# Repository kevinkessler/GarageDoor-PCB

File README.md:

PCB Eagle Files for Garage Door Spark Core project

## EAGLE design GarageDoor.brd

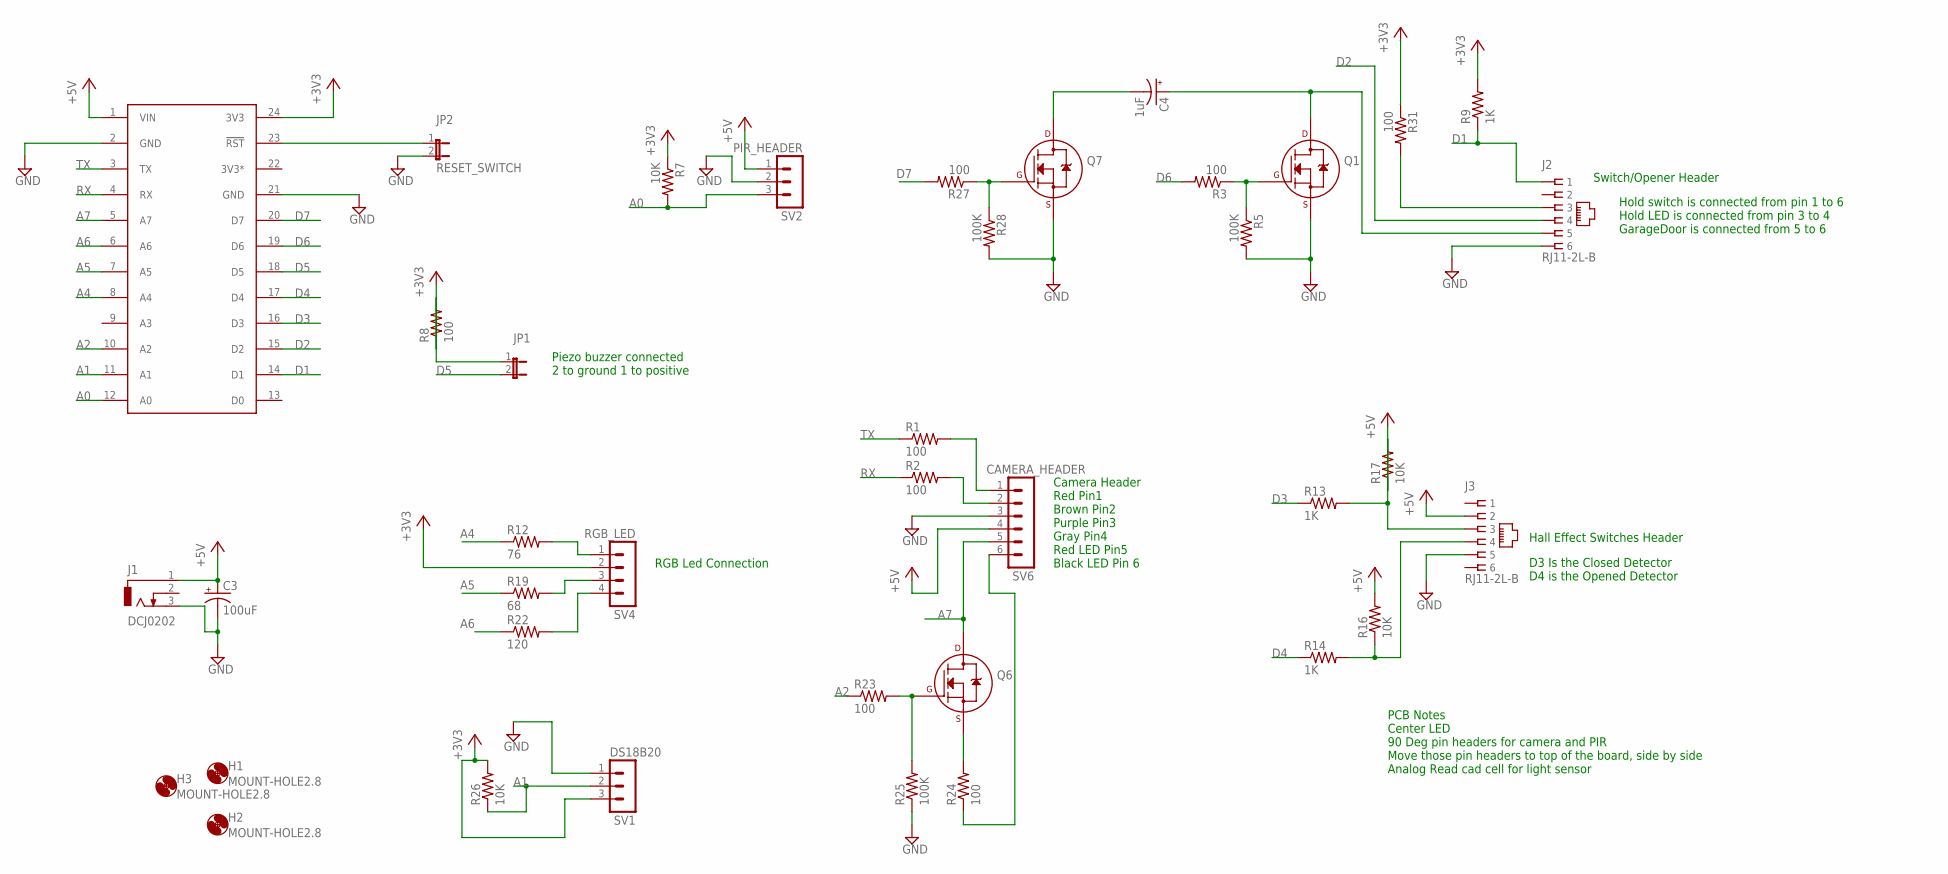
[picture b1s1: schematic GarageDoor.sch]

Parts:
C3: 100uF; E2,5-6E
C4: 1uF; E2,5-6E
H1, H2, H3: MOUNT-HOLE2.8; 2,8
J1: DCJ0202
J2, J3: RJ11-2L-B; RJ11-NO_SHIELD
JP1: JP1E; JP1
JP2: RESET_SWITCH; JP1
Q1, Q6, Q7: 2N7000_SOT23; SOT-23
R1, R2, R3, R8, R23, R24, R27, R31: 100; R0805
R5, R25, R28: 100K; R0805
R7, R16, R17, R26: 10K; R0805
R9, R13, R14: 1K; R0805
R12: 76; R0805
R19: 68; R0805
R22: 120; R0805
SC1: SPARK_CORECORE; SPARK_CORE
SV1: DS18B20; MA03-1
SV2: PIR_HEADER; MA03-1
SV4: RGB_LED; MA04-1
SV6: CAMERA_HEADER; MA06-1

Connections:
3V3*: SC1.22 (3V3*)
+3V3: R7.1, R8.1, R9.2, R26.2, R31.1, SC1.24 (3V3), SV1.3, SV4.2
+5V: C3.+, J1.1, J3.2, R16.2, R17.1, SC1.1 (VIN), SV2.1, SV6.4
A0: R7.2, SC1.12 (A0), SV2.3
A1: R26.1, SC1.11 (A1), SV1.2
A2: R23.1, SC1.10 (A2)
A4: R12.1, SC1.8 (A4)
A5: R19.1, SC1.7 (A5)
A6: R22.1, SC1.6 (A6)
A7: Q6.3 (D), SC1.5 (A7), SV6.5
D1: J2.1, R9.1, SC1.14 (D1)
D2: J2.4, SC1.15 (D2)
D3: R13.1, SC1.16 (D3)
D4: R14.1, SC1.17 (D4)
D5: JP1.2, SC1.18 (D5)
D6: R3.2, SC1.19 (D6)
D7: R27.2, SC1.20 (D7)
GND: C3.-, J1.3, J2.6, J3.5, JP2.2, Q1.2 (S), Q7.2 (S), R5.2, R25.1, R28.2, SC1.2 (GND), SC1.21 (GND), SV1.1, SV2.2, SV6.3
unnamed: Q1.1 (G), R3.1, R5.1
unnamed: R22.2, SV4.4
unnamed: R12.2, SV4.1
unnamed: R19.2, SV4.3
unnamed: Q7.1 (G), R27.1, R28.1
unnamed: J3.3, R13.2, R17.2
unnamed: J3.4, R14.2, R16.1
unnamed: C4.+, J2.5, Q1.3 (D)
unnamed: JP1.1, R8.2
unnamed: R1.2, SV6.1
unnamed: R2.2, SV6.2
unnamed: Q6.2 (S), R24.2
unnamed: R24.1, SV6.6
unnamed: Q6.1 (G), R23.2, R25.2
unnamed: JP2.1, SC1.23 (!RST)
unnamed: C4.-, Q7.3 (D)
unnamed: J2.3, R31.2
RX: R2.1, SC1.4 (RX)
TX: R1.1, SC1.3 (TX)

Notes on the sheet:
Hall Effect Switches Header
RGB Led Connection
D3 Is the Closed Detector D4 is the Opened Detector
Switch/Opener Header
Hold switch is connected from pin 1 to 6 Hold LED is connected from pin 3 to 4 GarageDoor is connected from 5 to 6
Piezo buzzer connected 2 to ground 1 to positive
Camera Header Red Pin1 Brown Pin2 Purple Pin3 Gray Pin4 Red LED Pin5 Black LED Pin 6
PCB Notes Center LED 90 Deg pin headers for camera and PIR Move those pin headers to top of the board, side by side Analog Read cad cell for light sensor

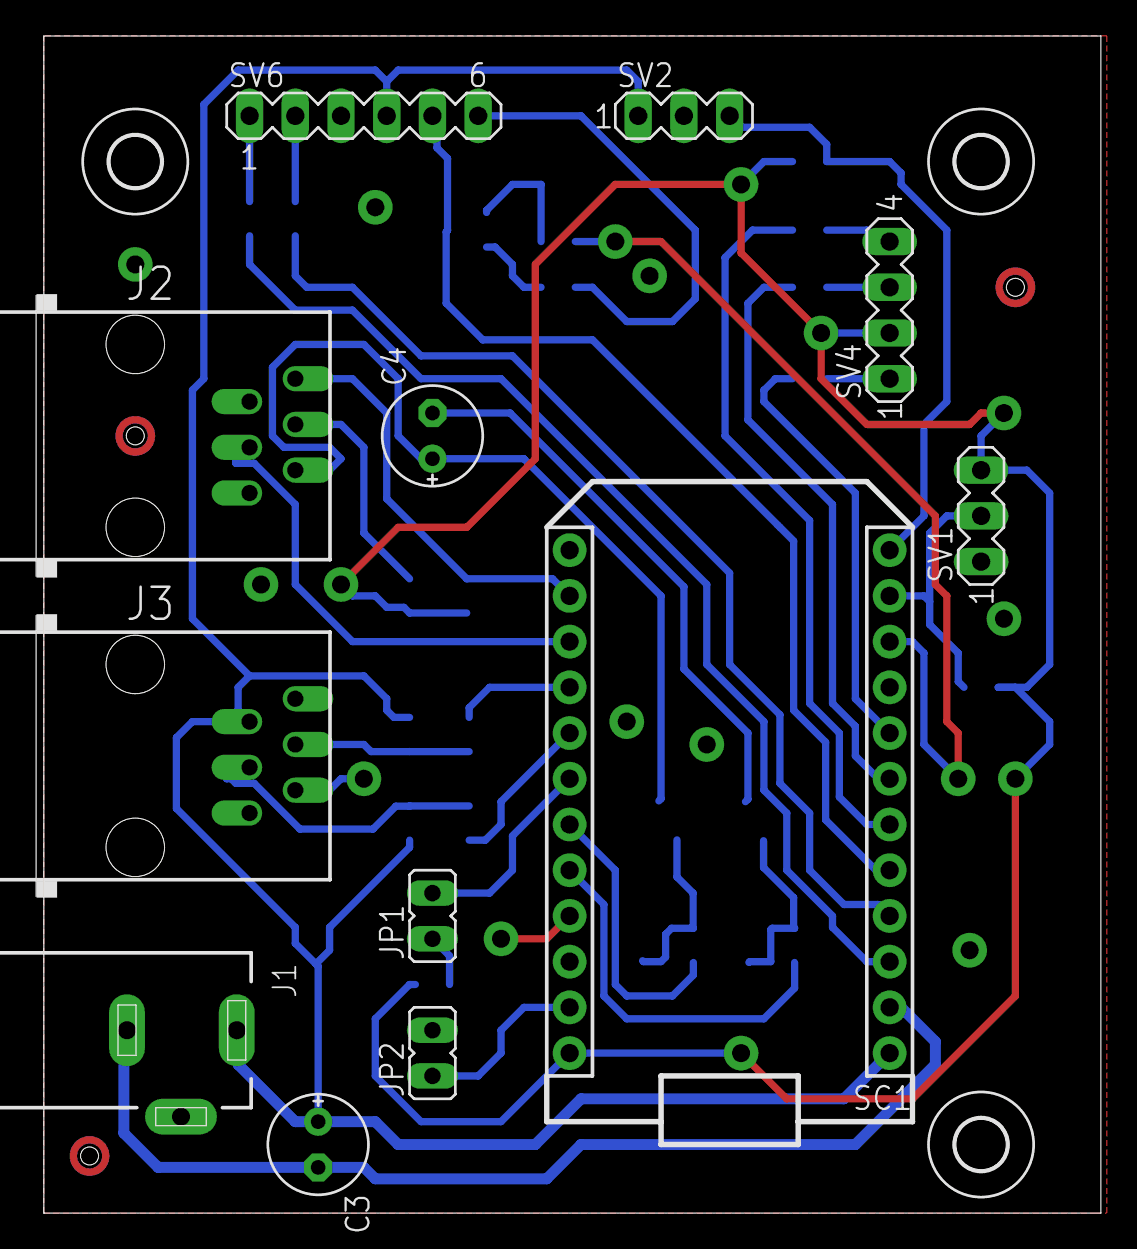
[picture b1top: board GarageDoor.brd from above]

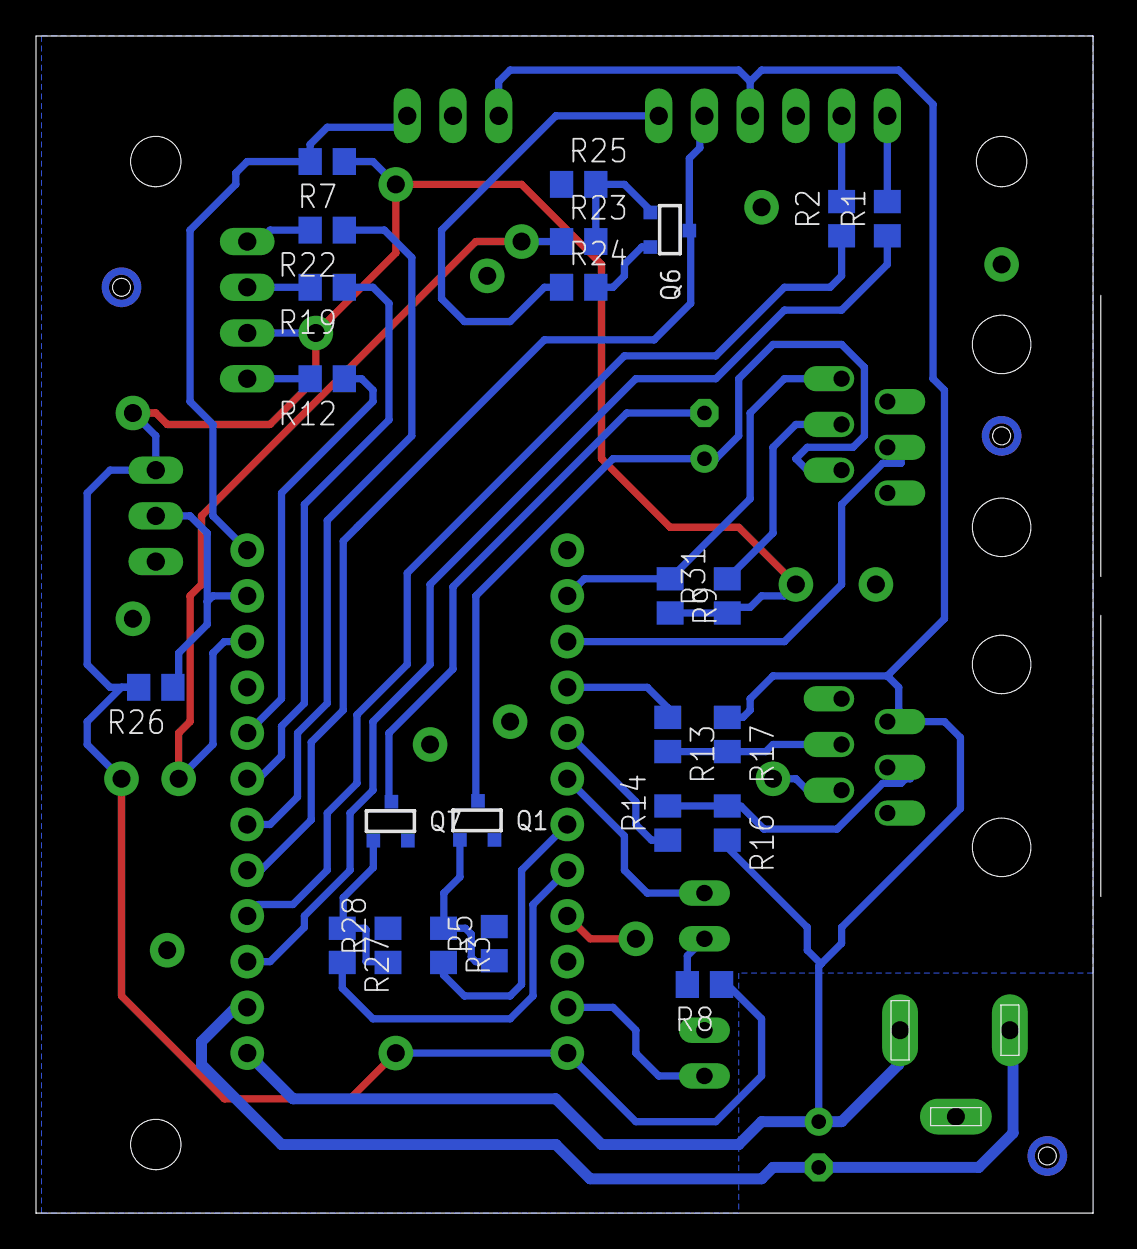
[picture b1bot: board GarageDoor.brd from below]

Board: 2 copper layers, 58.7 x 65.4 mm, 39 parts (24 on the bottom side), 36 nets.

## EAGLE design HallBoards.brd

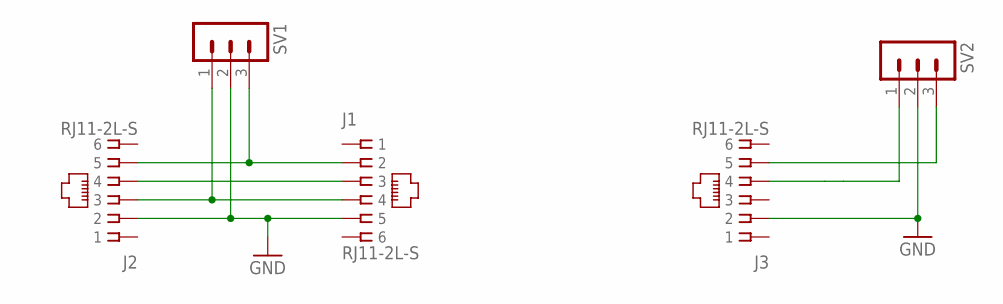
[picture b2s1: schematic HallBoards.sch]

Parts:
J1, J2, J3: RJ11-2L-S; RJ11-NO_SHIELD
SV1, SV2: MA03-1

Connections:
GND: J1.5, J2.2, J3.2, SV1.2, SV2.2
unnamed: J1.4, J2.3, SV1.1
unnamed: J1.3, J2.4
unnamed: J1.2, J2.5, SV1.3
unnamed: J3.5, SV2.3
unnamed: J3.4, SV2.1

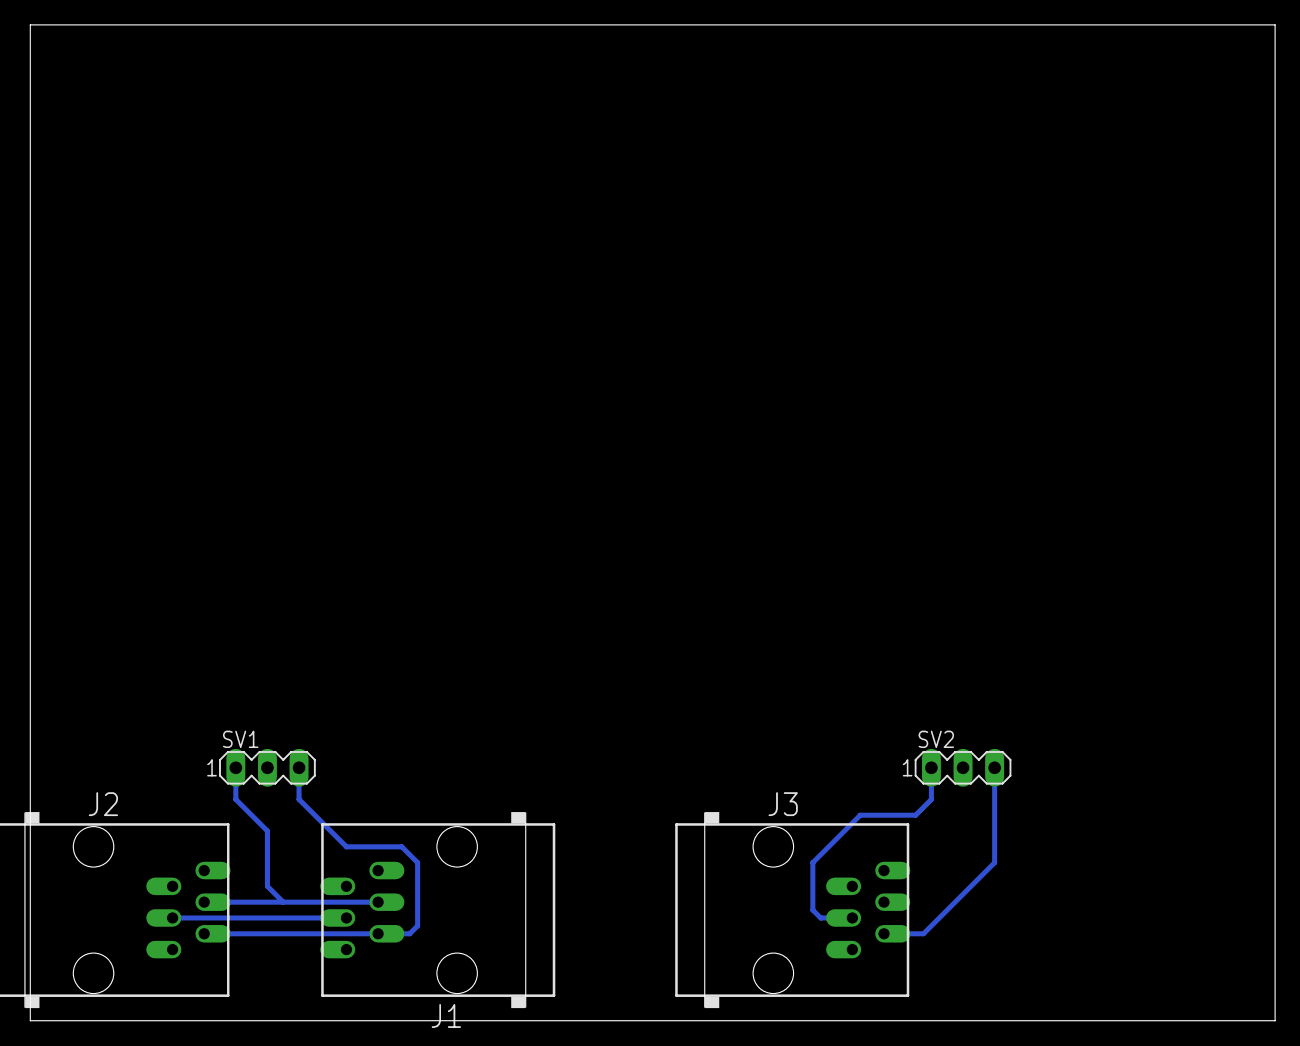
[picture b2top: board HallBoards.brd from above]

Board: 2 copper layers, 100.0 x 80.0 mm, 5 parts (0 on the bottom side), 6 nets.

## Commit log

2015-02-05 LED_RGB Circuit
2015-02-06 I hate git
2015-02-06 5V Regulator
2015-02-06 Hall Effect Circuitry
2015-02-11 Added Alarm and Hold
2015-02-27 Camera Added
2015-03-02 Add Temperature Sensor
2015-03-04 Added 78LM and Hold LED
2015-03-10 Created PCB
2015-08-05 Create PDF
2015-08-05 Hall Boards PCFs
2015-08-05 Liftmaster PDF
